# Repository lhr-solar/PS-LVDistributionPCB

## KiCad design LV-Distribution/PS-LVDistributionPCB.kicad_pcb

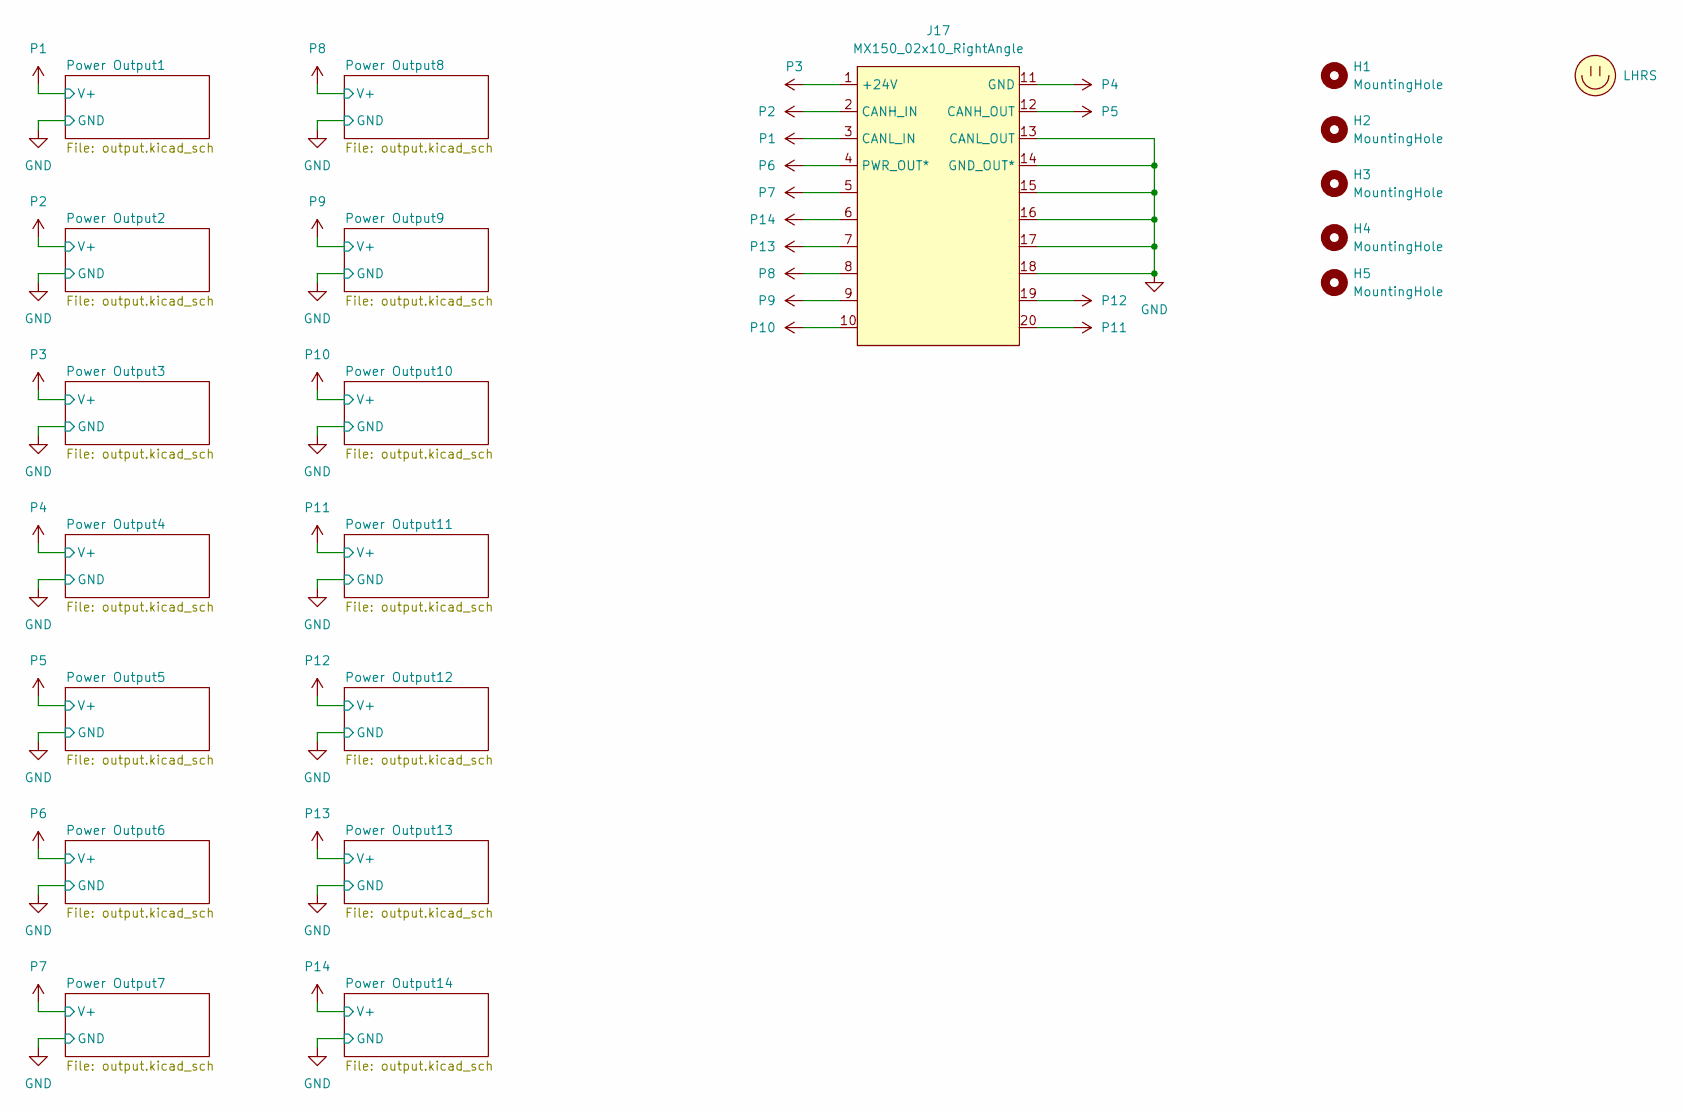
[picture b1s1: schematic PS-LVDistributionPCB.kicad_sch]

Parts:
H1, H2, H3, H4, H5: MountingHole; MountingHole_3.2mm_M3
J17: MX150_02x10_RightAngle; CONN_SD-34829-001_20_ST_MOL
LOGO1: LHRS; LHRs_LOGO

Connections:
GND: J17.13 (CANL_OUT), J17.14 (GND_OUT*), J17.15, J17.16, J17.17, J17.18; also elsewhere on the board
P1: J17.3 (CANL_IN); also elsewhere on the board
P2: J17.2 (CANH_IN); also elsewhere on the board
P3: J17.1 (+24V); also elsewhere on the board
P4: J17.11 (GND); also elsewhere on the board
P5: J17.12 (CANH_OUT); also elsewhere on the board
P6: J17.4 (PWR_OUT*); also elsewhere on the board
P7: J17.5; also elsewhere on the board
P8: J17.8; also elsewhere on the board
P9: J17.9; also elsewhere on the board
P10: J17.10; also elsewhere on the board
P11: J17.20; also elsewhere on the board
P12: J17.19; also elsewhere on the board
P13: J17.7; also elsewhere on the board
P14: J17.6; also elsewhere on the board

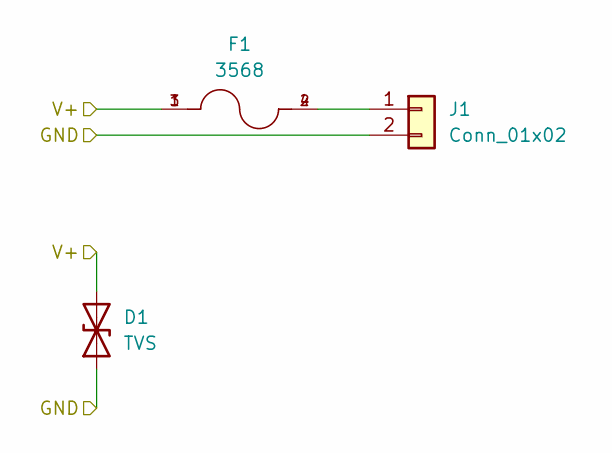
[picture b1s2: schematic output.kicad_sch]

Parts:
D1: TVS; D_SMB
F1: 3568; FUSE_3568
J1: Conn_01x02; AMASS_XT30UPB-M_1x02_P5.0mm_Vertical

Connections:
GND: D1.1 (A1), J1.2; also elsewhere on the board
unnamed: F1.2, F1.4, J1.1
P1: D1.2 (A2), F1.1, F1.3; also elsewhere on the board

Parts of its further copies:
D2, D3, D4, D5, D6, D7, D8, D9, D10, D11, D12, D13, D14: TVS; D_SMB
F2, F3, F4, F5, F6, F7, F8, F9, F10, F11, F12, F13, F14: 3568; FUSE_3568
J2, J3, J4, J5, J6, J7, J8, J9, J10, J11, J12, J13, J14: Conn_01x02; AMASS_XT30UPB-M_1x02_P5.0mm_Vertical

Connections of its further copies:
GND: D2.1 (A1), D3.1 (A1), D4.1 (A1), D5.1 (A1), D6.1 (A1), D7.1 (A1), D8.1 (A1), D9.1 (A1), D10.1 (A1), D11.1 (A1), D12.1 (A1), D13.1 (A1), D14.1 (A1), J2.2, J3.2, J4.2, J5.2, J6.2, J7.2, J8.2, J9.2, J10.2, J11.2, J12.2, J13.2, J14.2; also elsewhere on the board
unnamed: F2.2, F2.4, J2.1
unnamed: F3.2, F3.4, J3.1
unnamed: F4.2, F4.4, J4.1
unnamed: F5.2, F5.4, J5.1
unnamed: F6.2, F6.4, J6.1
unnamed: F7.2, F7.4, J7.1
unnamed: F8.2, F8.4, J8.1
unnamed: F9.2, F9.4, J9.1
unnamed: F10.2, F10.4, J10.1
unnamed: F11.2, F11.4, J11.1
unnamed: F12.2, F12.4, J12.1
unnamed: F13.2, F13.4, J13.1
unnamed: F14.2, F14.4, J14.1
P2: D2.2 (A2), F2.1, F2.3; also elsewhere on the board
P3: D3.2 (A2), F3.1, F3.3; also elsewhere on the board
P4: D4.2 (A2), F4.1, F4.3; also elsewhere on the board
P5: D5.2 (A2), F5.1, F5.3; also elsewhere on the board
P6: D6.2 (A2), F6.1, F6.3; also elsewhere on the board
P7: D7.2 (A2), F7.1, F7.3; also elsewhere on the board
P8: D8.2 (A2), F8.1, F8.3; also elsewhere on the board
P9: D9.2 (A2), F9.1, F9.3; also elsewhere on the board
P10: D10.2 (A2), F10.1, F10.3; also elsewhere on the board
P11: D11.2 (A2), F11.1, F11.3; also elsewhere on the board
P12: D12.2 (A2), F12.1, F12.3; also elsewhere on the board
P13: D13.2 (A2), F13.1, F13.3; also elsewhere on the board
P14: D14.2 (A2), F14.1, F14.3; also elsewhere on the board

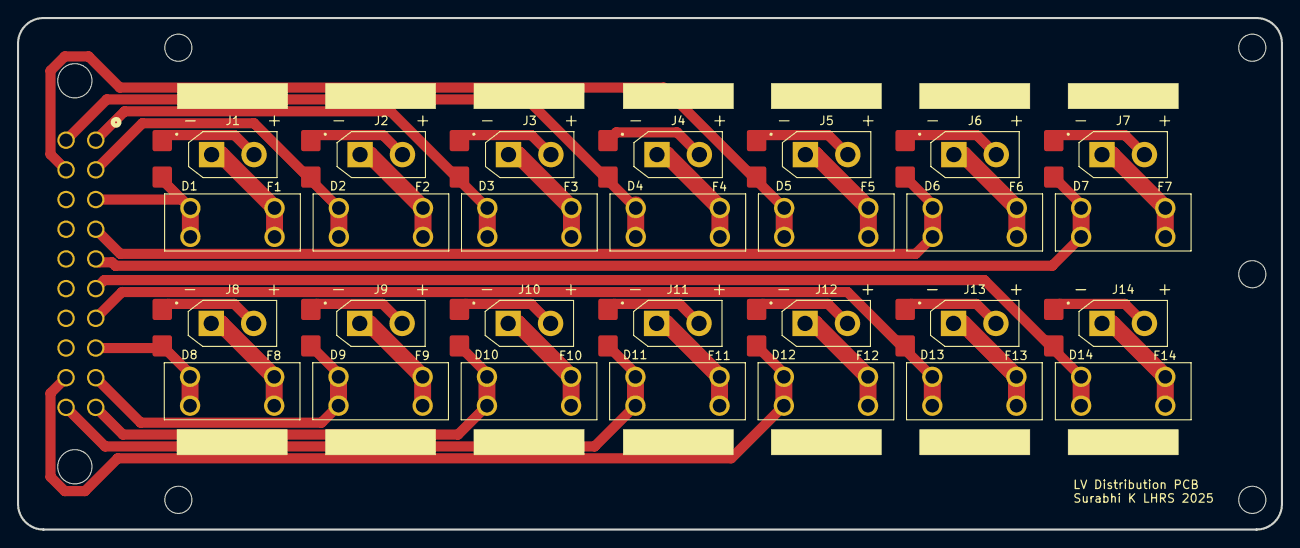
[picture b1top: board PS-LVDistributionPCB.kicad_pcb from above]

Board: 2 copper layers, 149.0 x 60.3 mm, 49 parts (1 on the bottom side), 29 nets.

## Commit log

2024-12-14 LED fuse inidicator
2024-12-14 removed LEDs
2025-01-17 finished schematic
2025-01-18 finished pcb
2025-01-18 more fill zones
2025-01-21 rearranged fuses on the back and and connectors on the front for improved waterproofing
2025-01-25 reoriented fuses horizontally to fit enclosure dimensions
2025-01-25 realigned fill zones
2025-01-25 add connector footprints
2025-01-25 Fixed 3d models
2025-02-08 testing git commit
2025-02-08 Added optoisolators to ensure LED indicators are powered by critical power and only turn on when the fuse blows. Fuses and resistors on the back for waterproofing.
2025-02-08 fixed gitignore
2025-02-15 reshaped filled zones to add more copper for current flow
2025-02-15 changed fill zones
2025-05-27 solder bridges
2025-05-27 flipped conn side
2025-07-24 xt30s + right angle mx150 initial layout
2025-07-24 custom libs
2025-07-31 common gnd
2025-09-14 removed 2 outputs + smaller
2025-09-14 update modules
2025-09-14 kicad sharepoint
2025-09-14 3d model
2025-09-14 trace widths
2025-09-24 added TVS diodes and routed traces
2025-09-27 14 outputs with 2 row mx150 symbol
2025-09-27 added step file
2025-09-27 reset and rename
2025-09-27 better test board setup
2025-09-30 temp commit for branch change
2025-09-30 widened board for ptn
2025-09-30 board centered step
2025-10-05 fixed symbols + prelim layout
2025-10-07 updated symbols
2025-10-11 making files nicer
2025-10-11 test board gerbers
2025-10-11 file org again
2025-10-11 redo traces trial 1
2025-10-11 better layout but weird 3d stuff
2025-10-11 fixed 3d + gerbers
2025-10-11 fixed weird extra project
2025-10-11 labels for outputs + new gerbers
2025-10-11 jk fixed step
2025-10-25 lv distribution bom
2025-10-25 bom for fusebox + test board
2025-10-25 fixed tvs diode screw you ravi
2025-10-25 fixed tvs diode on fuseboard
2025-10-25 jk added gerbers + bom
